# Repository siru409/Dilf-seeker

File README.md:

# Dilf-seeker
A near field multi beam ultra wideband fmcw radar detector using a novel near field focussed rotman lens

# to do maybe Hardware:
1. RX input limiter (strong RF sources close to dish)
2. FPGA compute port (if 4096 point FFT is not sufficient)

# to understand:
1: LOW if image rejection (ADL5380ACPZ-R7)

# to do Hardware:
1. RF traces ??
2. RX Chain finish
3. TX pll dimensions
4. MCU peripherals
5. Confirm charge pump circuit

# board tests:
0. does Balun Transformer output match IQ demod input impedance (yes)
1. Coupled TX IQ demod input <13dbm?
2. Test supplies first, only then add 0 ohm resistors to power sensitive components

# Design choices to make

1. Buttler matrix vs rotman lens -> rotman lense (potentially more array ports within reasonable space)
2. Vivaldi vs Horn Array-> Vivaldi array -> can be implemented in single PCB
3. 2 elliptical dishes vs combined rxtx vs TX dish + 8 fixed RX horns
4. Inductitity values for RX/TX inline buffers
5. 10uF caps 0805 -> price

# User manual

# simulation results

# Filtering

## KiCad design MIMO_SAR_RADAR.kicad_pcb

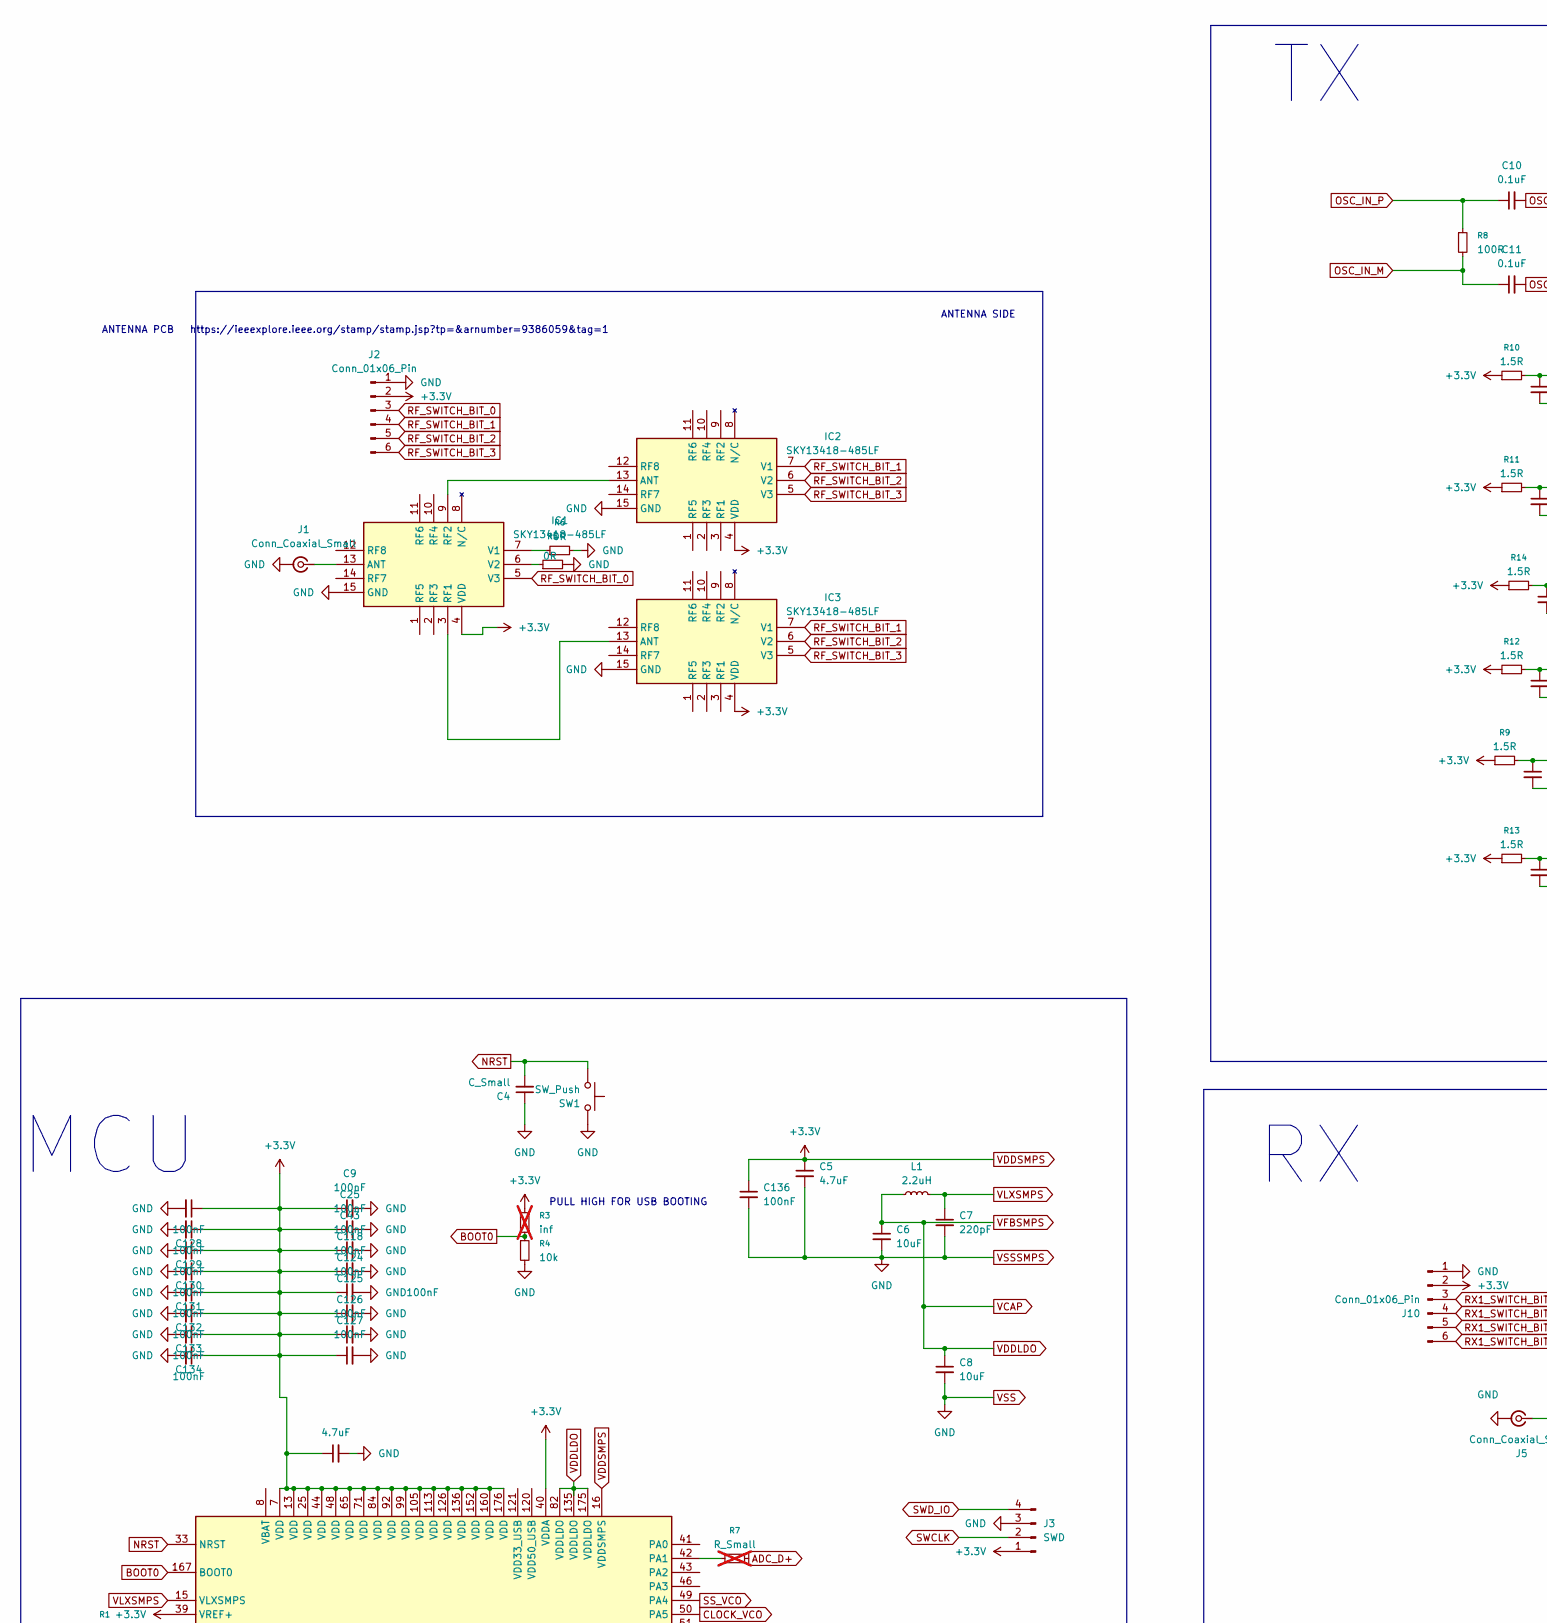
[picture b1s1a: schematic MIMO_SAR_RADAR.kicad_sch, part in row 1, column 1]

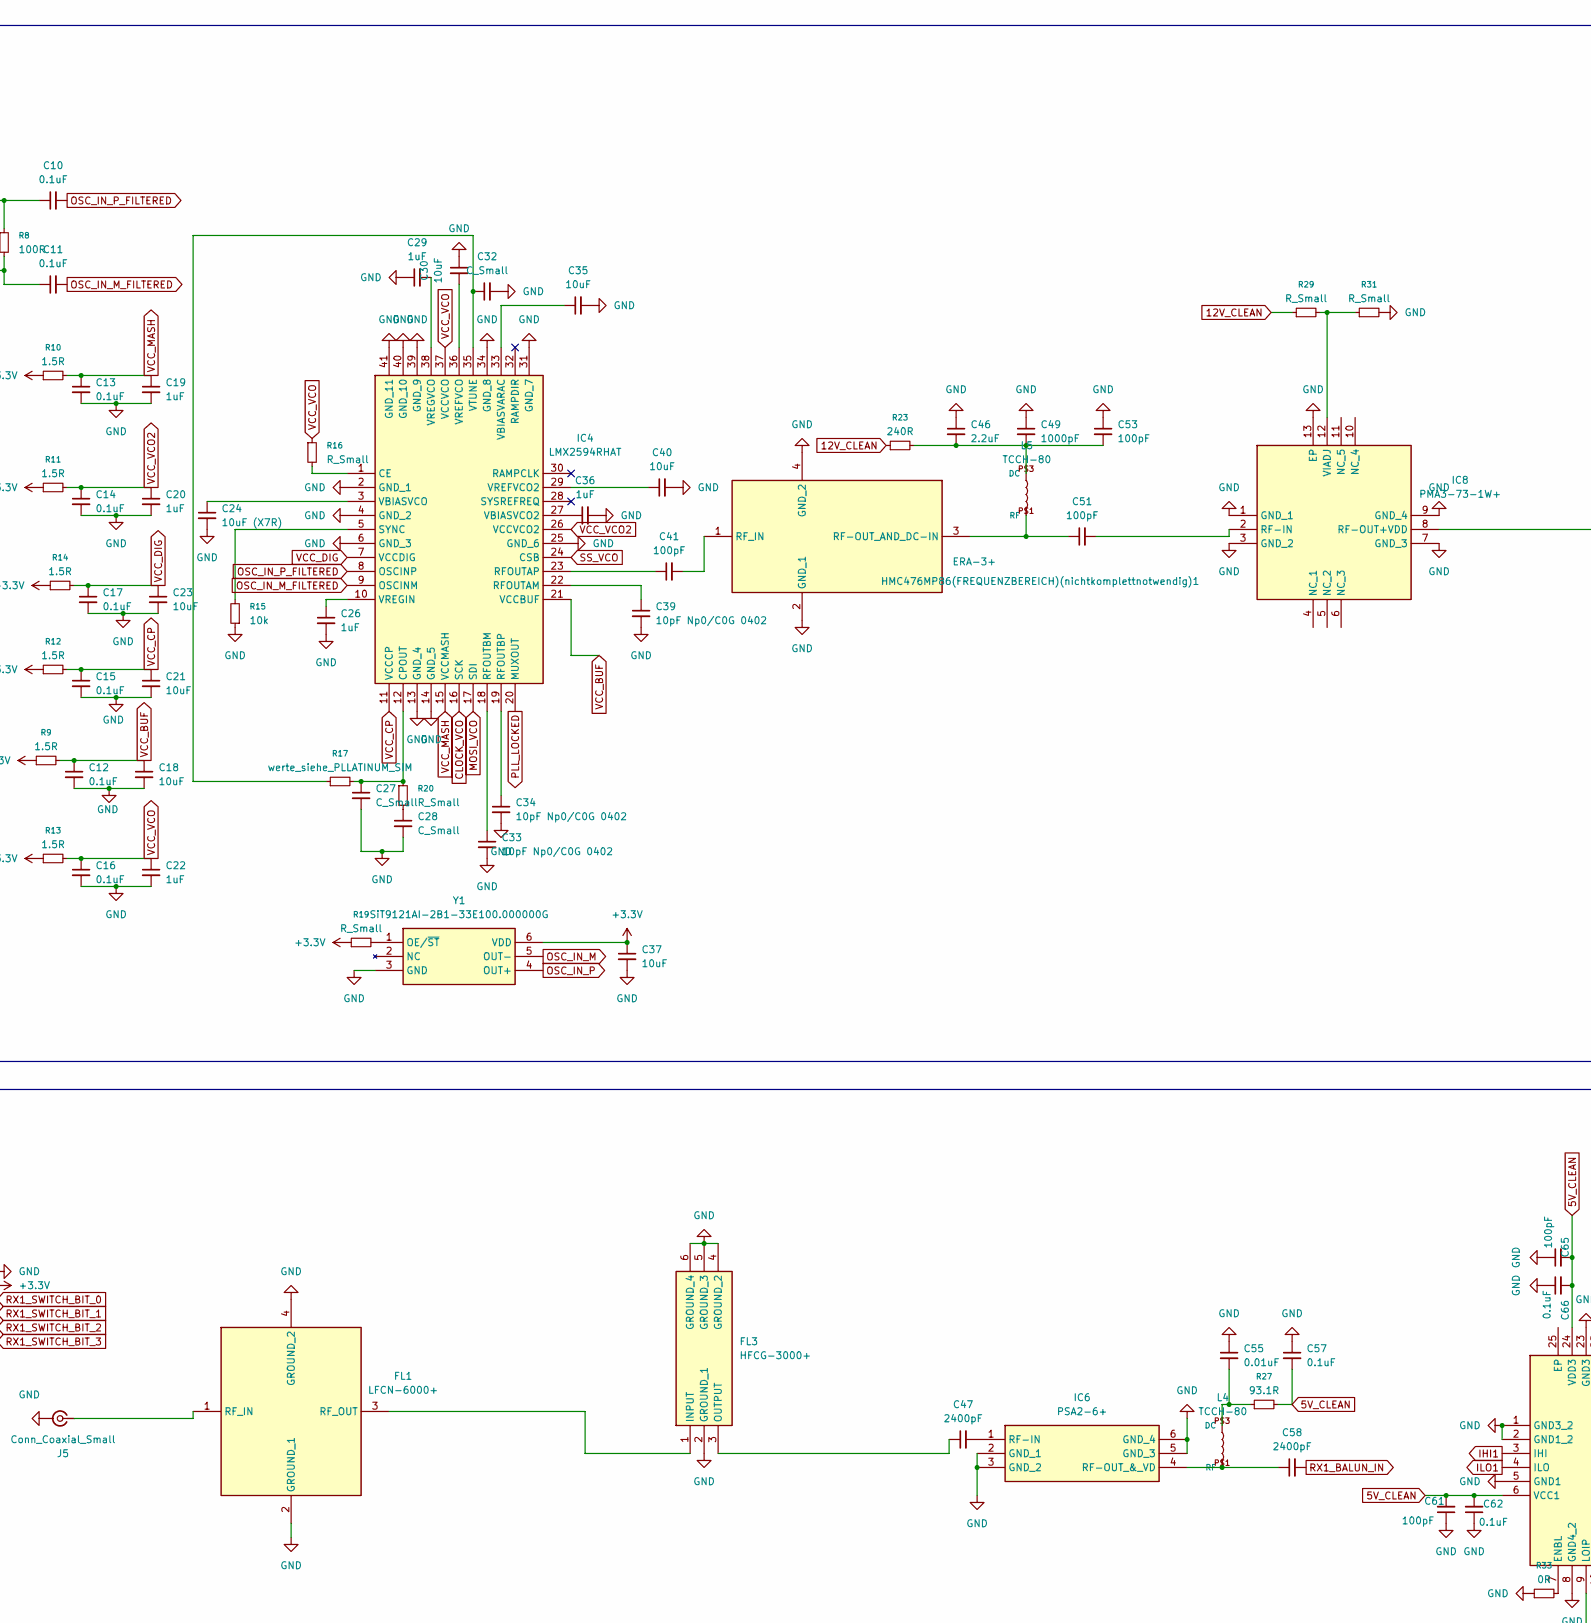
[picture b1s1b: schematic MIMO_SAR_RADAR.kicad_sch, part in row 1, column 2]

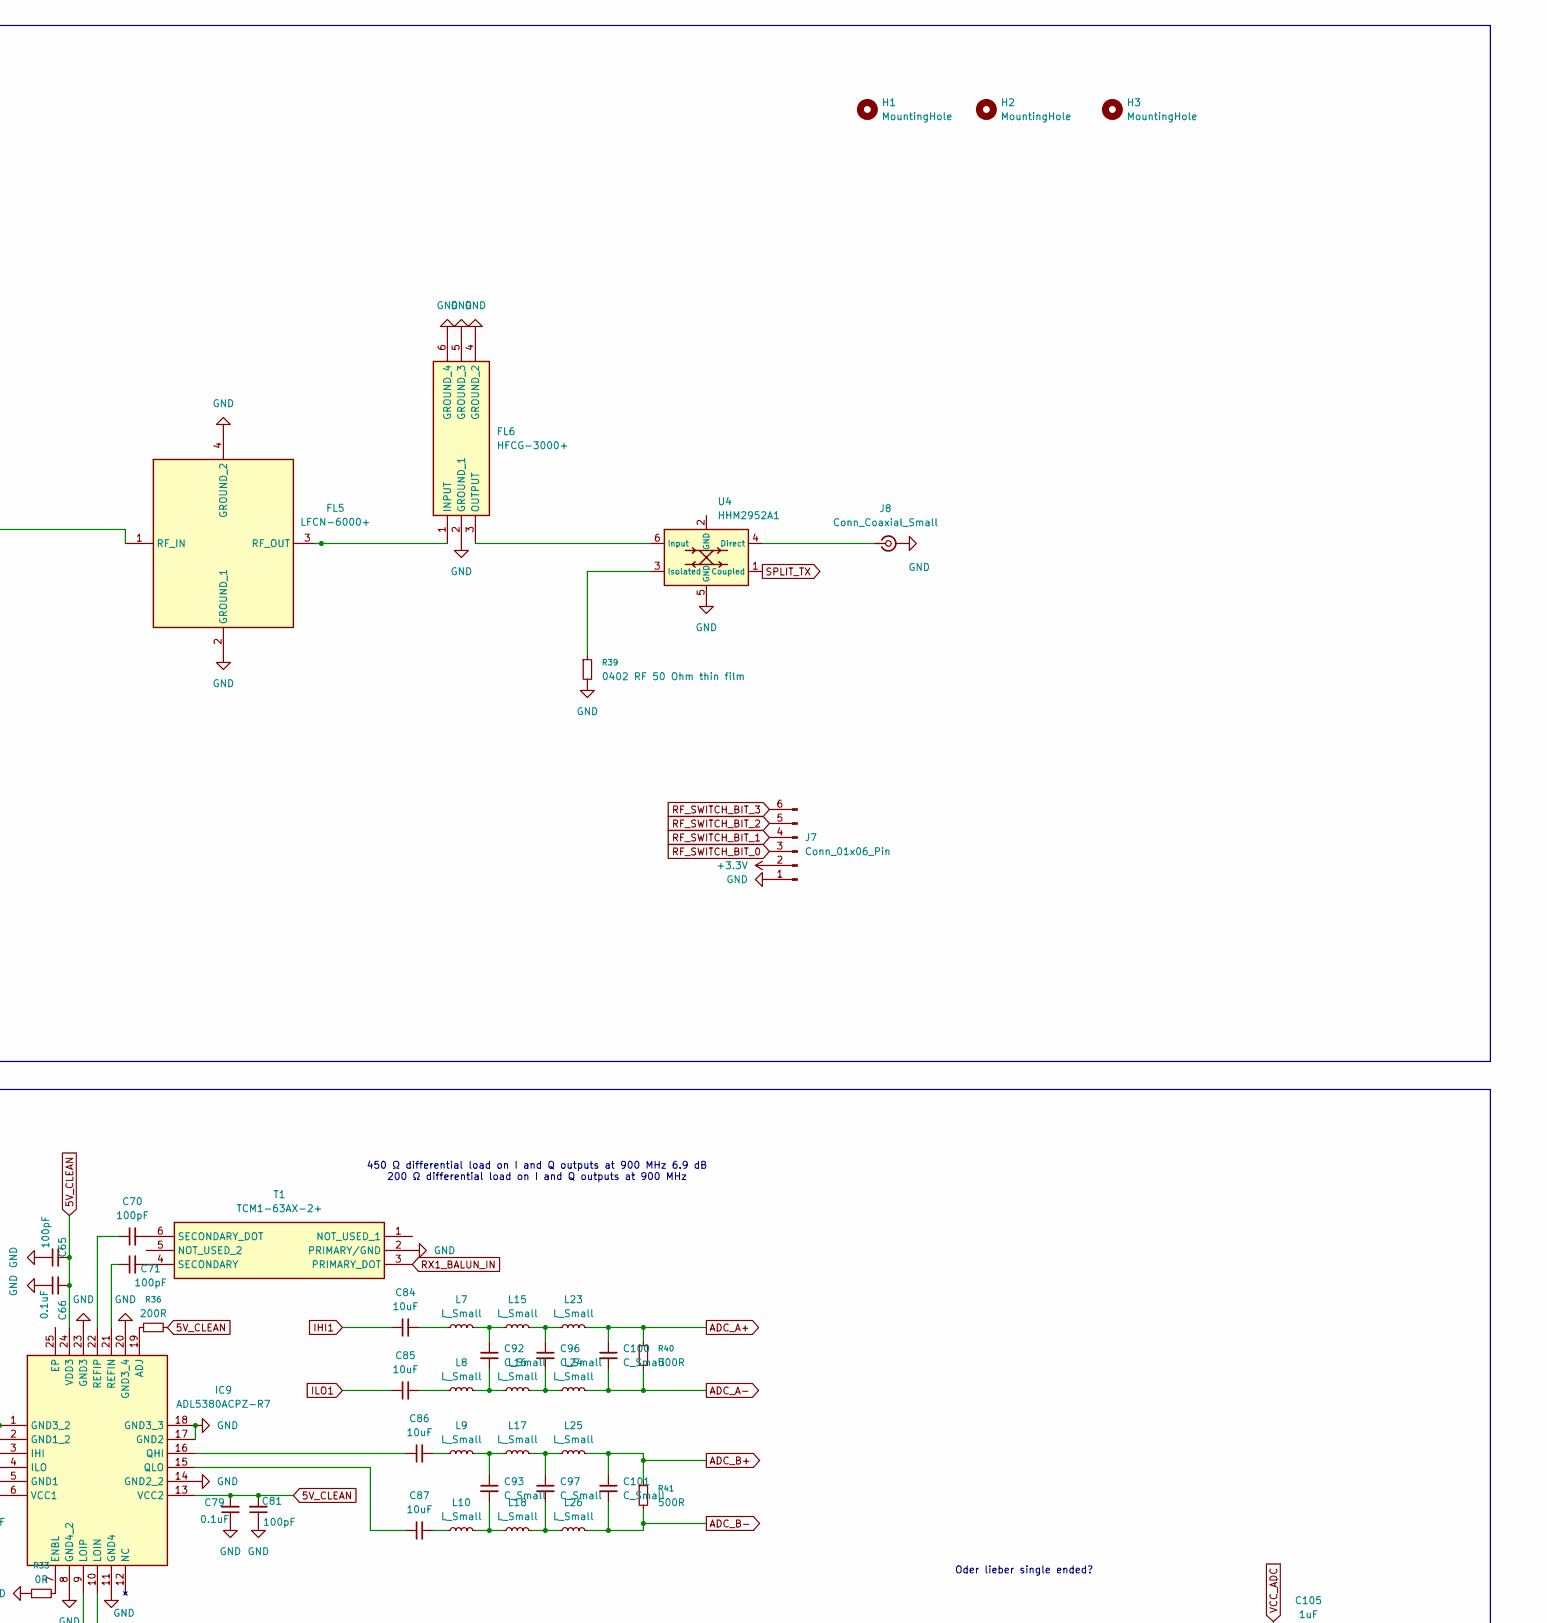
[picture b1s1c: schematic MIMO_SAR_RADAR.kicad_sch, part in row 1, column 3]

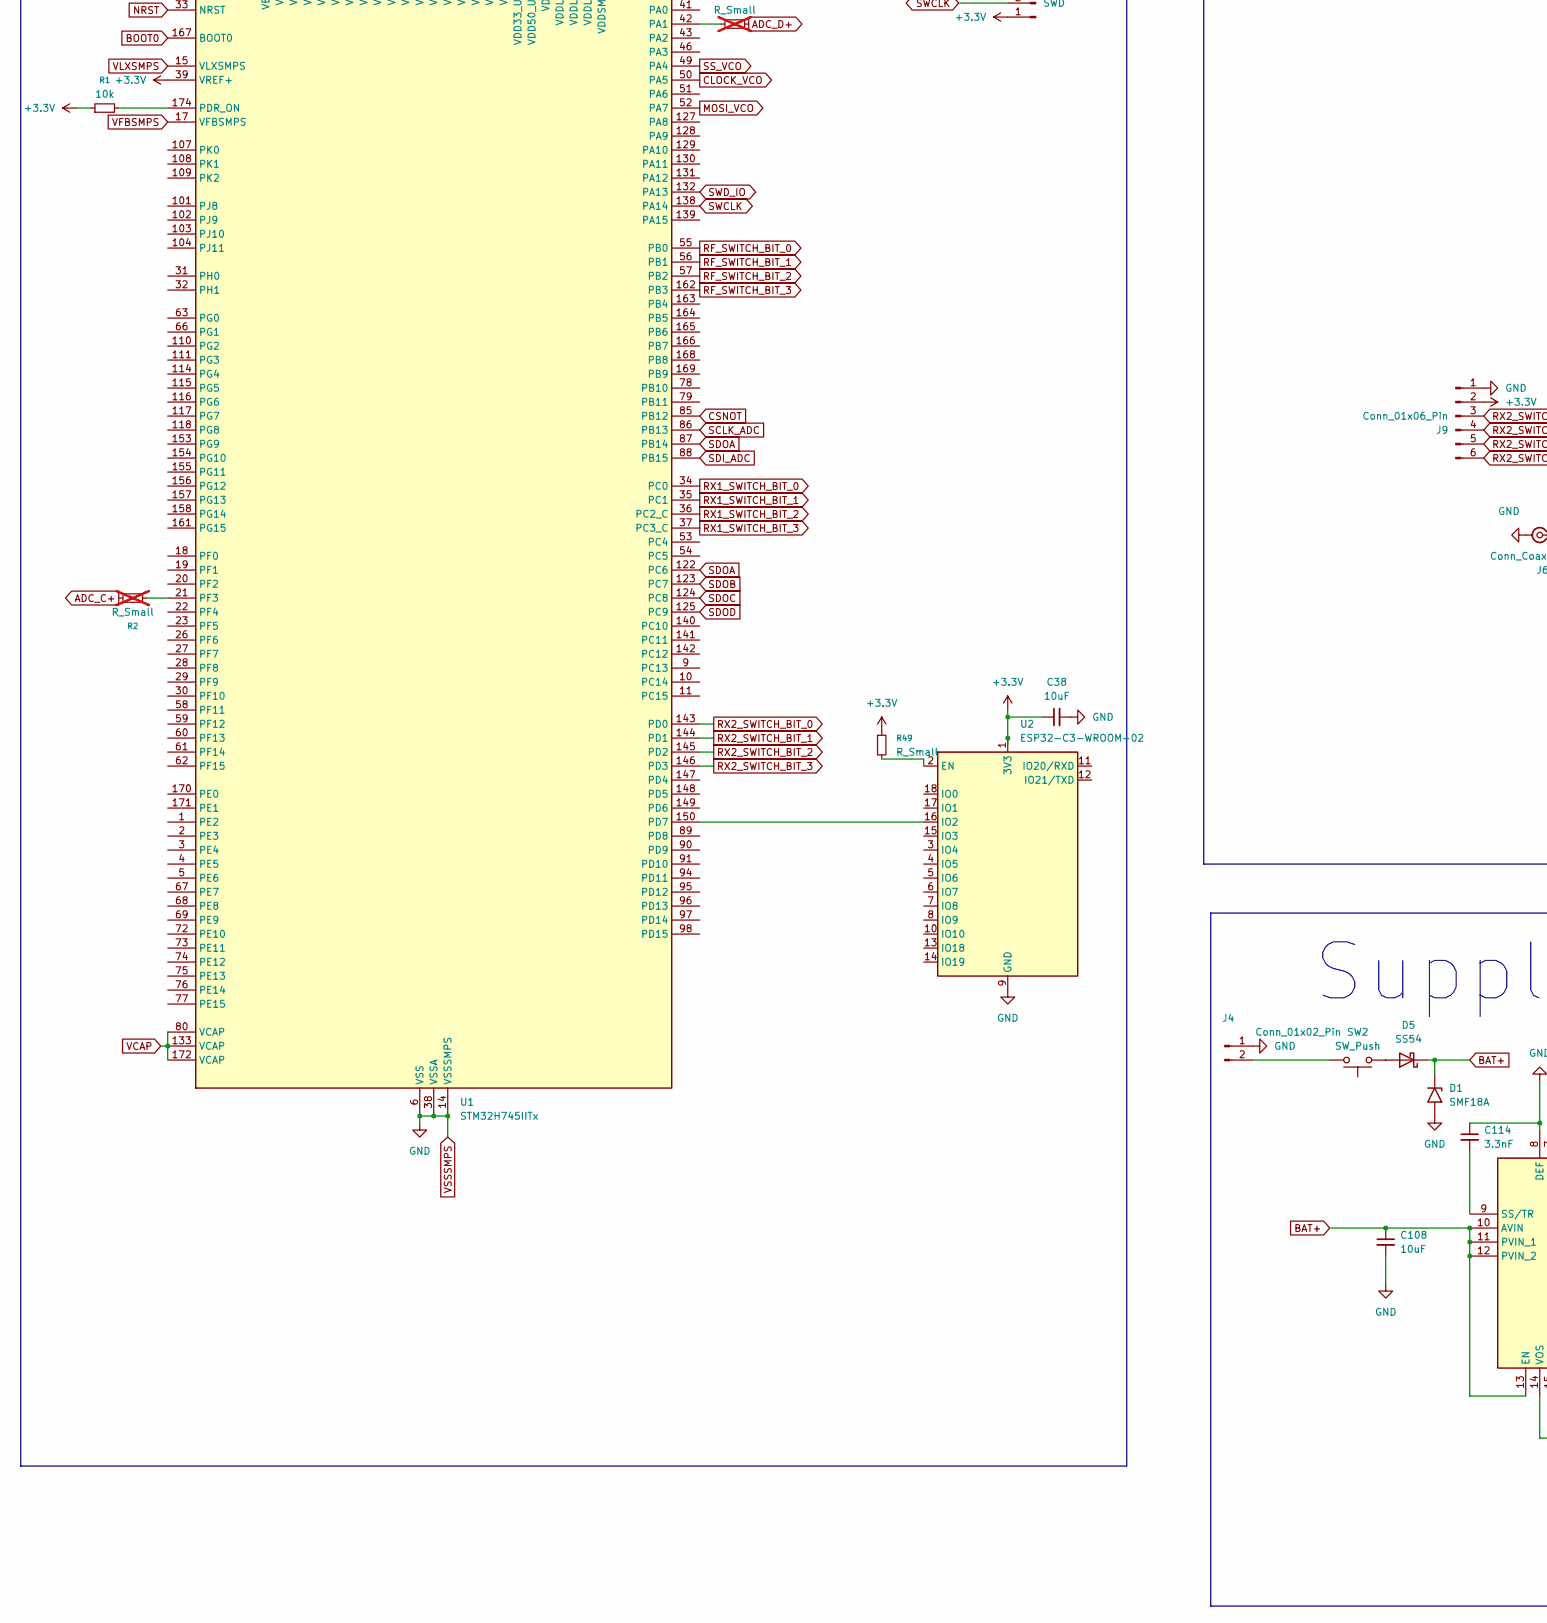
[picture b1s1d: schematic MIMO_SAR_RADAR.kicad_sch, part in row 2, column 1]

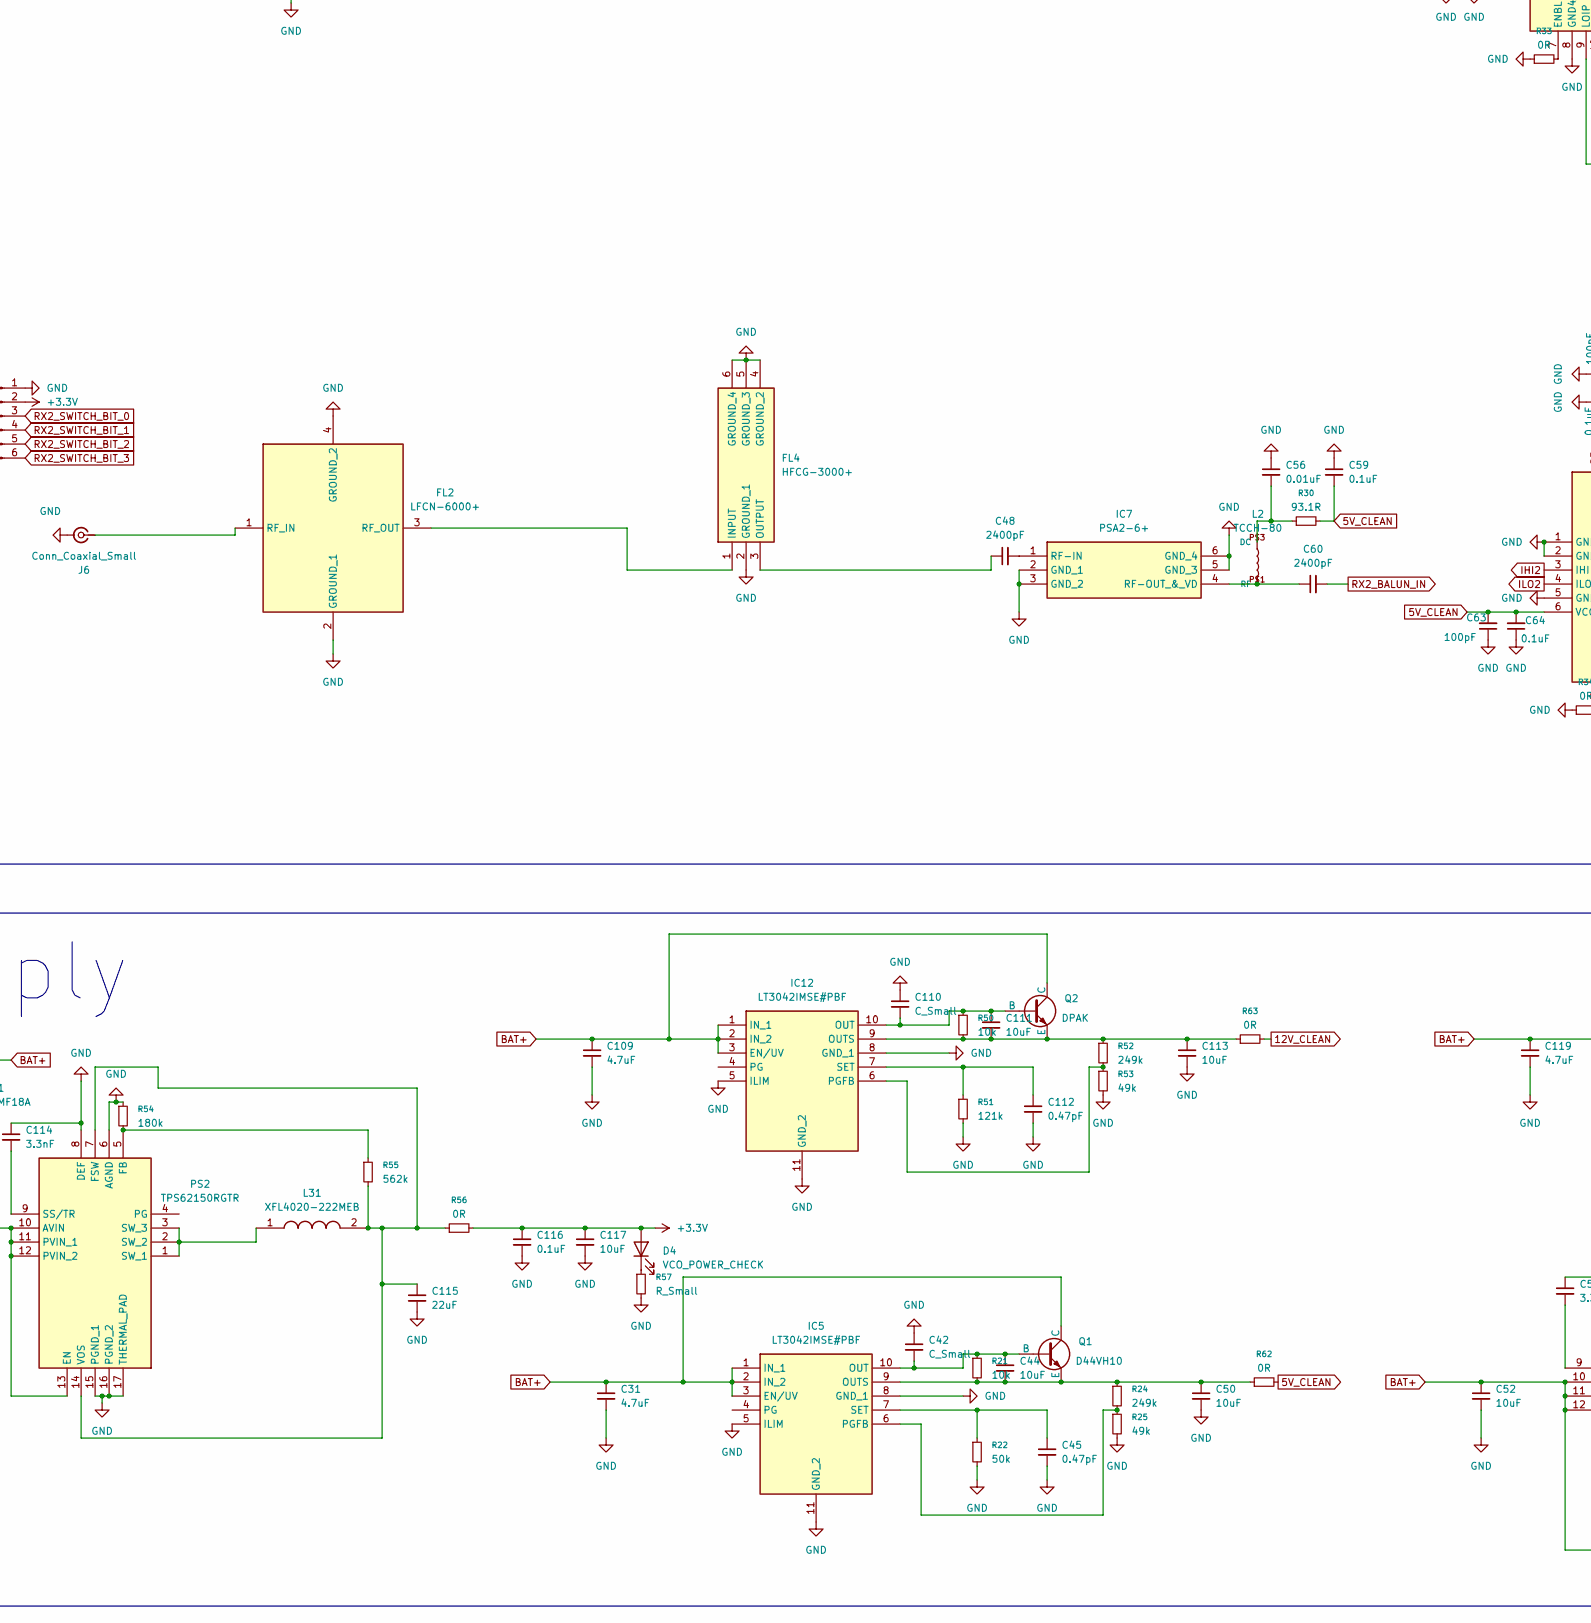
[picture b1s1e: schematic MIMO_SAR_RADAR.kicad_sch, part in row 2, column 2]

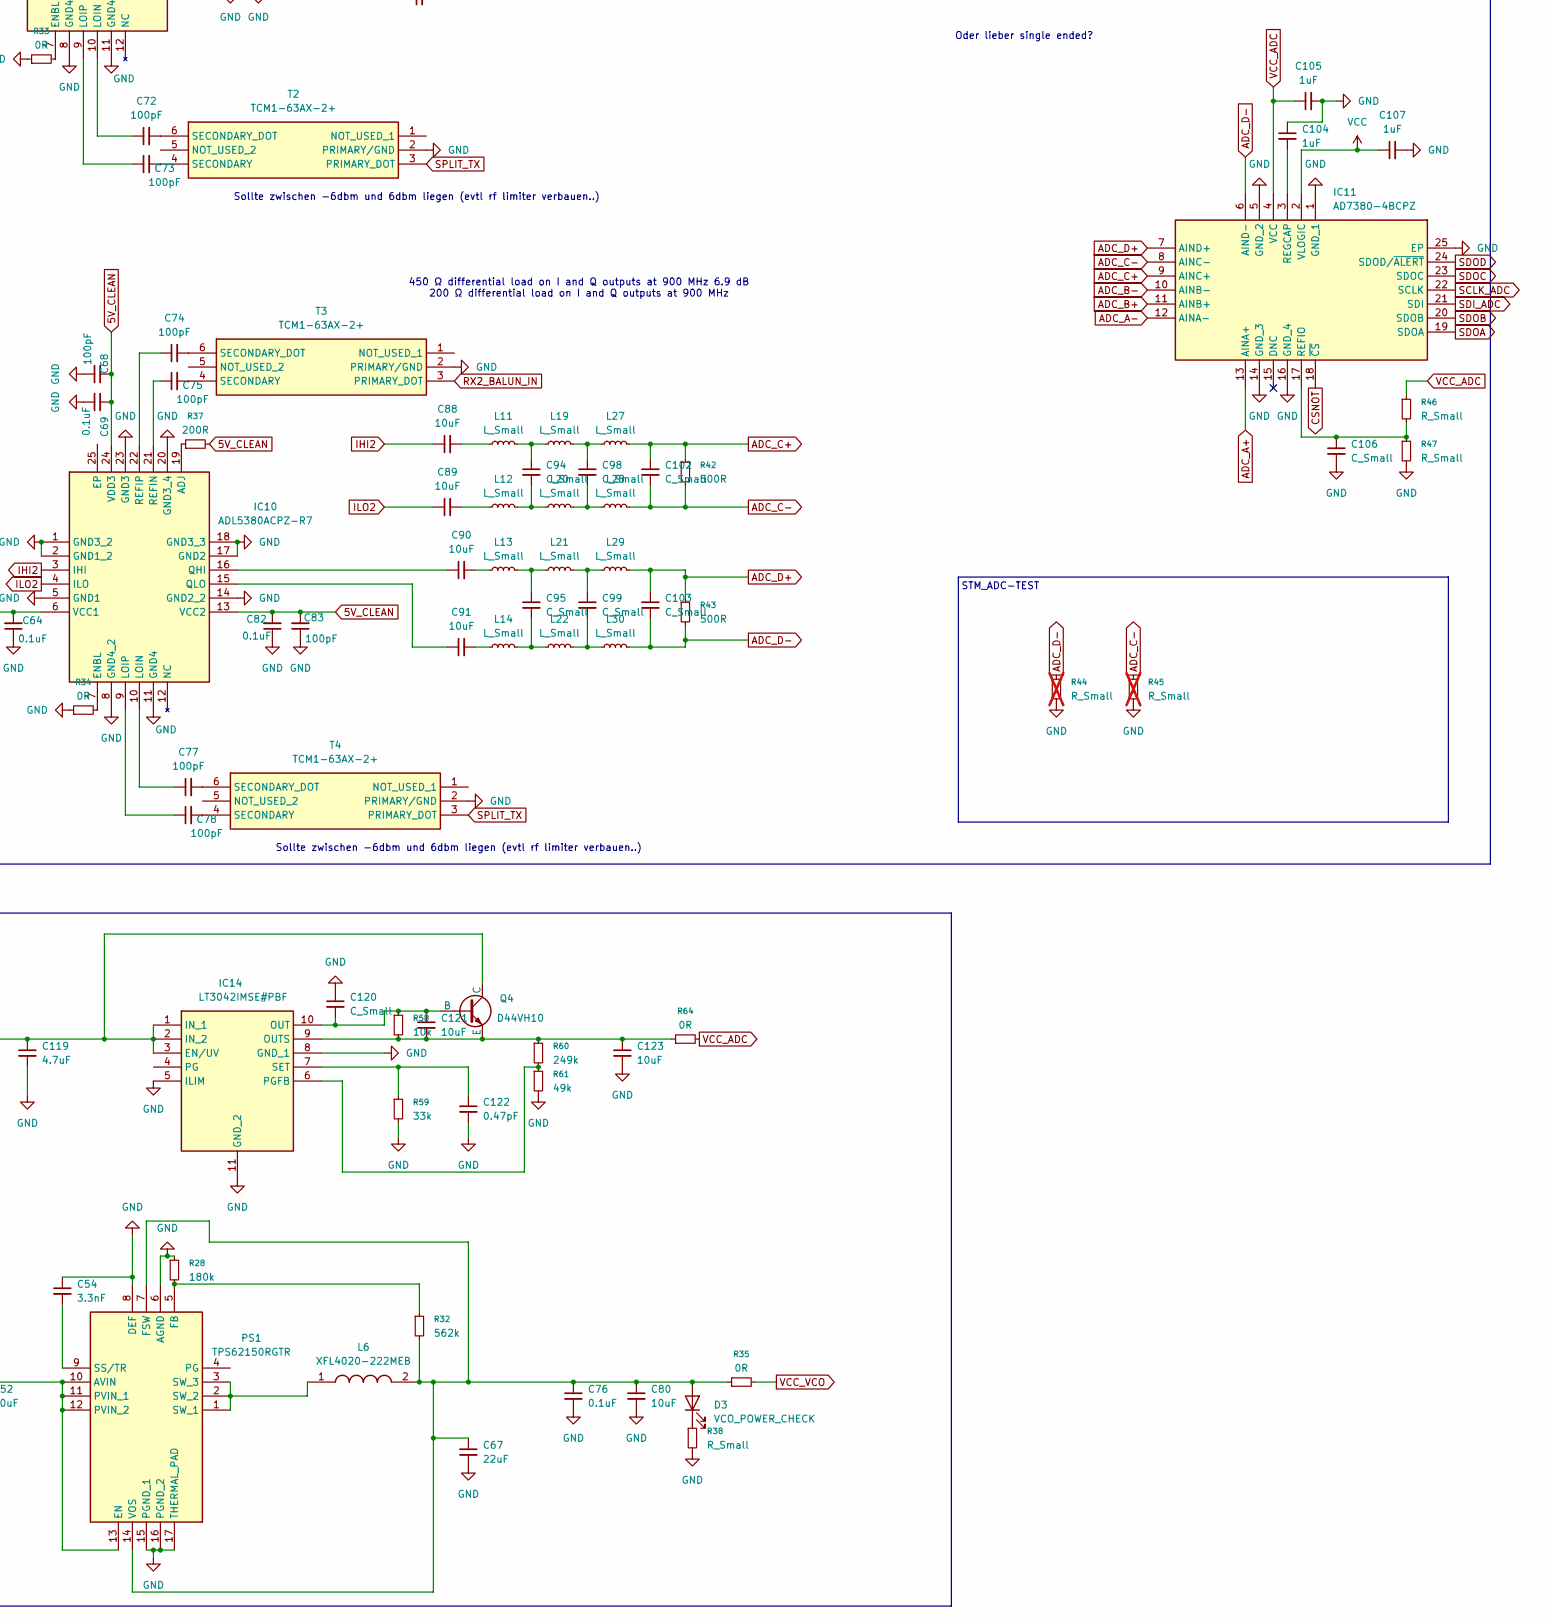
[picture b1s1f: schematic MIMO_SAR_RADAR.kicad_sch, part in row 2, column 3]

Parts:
C3, C5, C31, C109, C119: 4.7uF; C_0603_1608Metric
C4, C32, C42, C106, C110, C120: C_Small; C_0603_1608Metric
C6, C8, C18, C21, C23, C30, C35, C37, C38, C40, C44, C50, C52, C80, C108, C111, C113, C117, C121, C123: 10uF; C_0603_1608Metric
C7: 220pF; C_0603_1608Metric
C9, C25, C43, C118, C124, C125, C126, C127, C128, C129, C130, C131, C132, C133, C134, C135, C136: 100nF; C_0603_1608Metric
C10, C11: 0.1uF; C_0402_1005Metric
C12, C13, C14, C15, C16, C17, C57, C59, C62, C64, C66, C69, C76, C79, C82, C116: 0.1uF; C_0603_1608Metric
C19, C20, C22, C26, C29, C36, C104, C105, C107: 1uF; C_0603_1608Metric
C24: 10uF (X7R); C_0402_1005Metric
C27, C28, C92, C93, C94, C95, C96, C97, C98, C99, C100, C101, C102, C103: C_Small; C_0402_1005Metric
C33, C34, C39: 10pF Np0/C0G 0402; C_0402_1005Metric
C41, C51, C70, C71, C72, C73, C74, C75, C77, C78: 100pF; C_0402_1005Metric
C45, C112, C122: 0.47pF; C_0603_1608Metric
C46: 2.2uF; C_0603_1608Metric
C47, C58, C60: 2400pF; C_0402_1005Metric
C48: 2400pF; C_0603_1608Metric
C49: 1000pF; C_0603_1608Metric
C53, C61, C63, C65, C68, C81, C83: 100pF; C_0603_1608Metric
C54, C114: 3.3nF; C_0603_1608Metric
C55, C56: 0.01uF; C_0603_1608Metric
C67, C115: 22uF; C_0805_2012Metric
C84, C85, C86, C87, C88, C89, C90, C91: 10uF; C_0402_1005Metric
D1: SMF18A; D_SMF
D3, D4: VCO_POWER_CHECK; LED_0603_1608Metric
D5: SS54; D_SMA
FL1, FL2, FL5: LFCN-6000+; LFCN6000; Mouser Part Number 139-LFCN-6000
FL3, FL4, FL6: HFCG-3000+; HFCG3000; Mouser Part Number 139-HFCG-3000+
H1, H2, H3: MountingHole; MountingHole_3.2mm_M3_DIN965_Pad
HMC476MP86(FREQUENZBEREICH)(nichtkomplettnotwendig)1: ERA-3+; ERA3; Mouser Part Number 139-ERA-3
IC1, IC2, IC3: SKY13418-485LF; SKY13418485LF; Mouser Part Number 873-SKY13418-485LF
IC4: LMX2594RHAT; QFN-40-1EP_6x6mm_P0.5mm_EP4.6x4.6mm; Mouser Part Number 595-LMX2594RHAT
IC5, IC12, IC14: LT3042IMSE#PBF; SOP50P490X110-11N; Mouser Part Number 584-LT3042IMSE#PBF
IC6, IC7: PSA2-6+; SOT65P215X100-6N; Mouser Part Number 139-PSA2-6+
IC8: PMA3-73-1W+; QFN51P300X300X89-13N; Manufacturer_Part_Number PMA3-73-1W+
IC9, IC10: ADL5380ACPZ-R7; QFN50P400X400X100-25N; Mouser Part Number 584-ADL5380ACPZ-R7
IC11: AD7380-4BCPZ; QFN50P400X400X60-25N-D; Mouser Part Number 584-AD7380-4BCPZ
J1, J5, J6, J8: Conn_Coaxial_Small; SMA_Amphenol_132289_EdgeMount
J2, J7, J9, J10: Conn_01x06_Pin; JST_PH_B6B-PH-K_1x06_P2.00mm_Vertical
J3: SWD; JST_XH_B4B-XH-A_1x04_P2.50mm_Vertical
J4: Conn_01x02_Pin; AMASS_XT60-M_1x02_P7.20mm_Vertical
L1: 2.2uH; L_0805_2012Metric_Pad1.15x1.40mm_HandSolder
L2, L4, L5: TCCH-80; GU1604
L6, L31: XFL4020-222MEB; XFL4020-222ME; Mouser Part Number 994-XFL4020-222MEB
L7, L8, L9, L10, L11, L12, L13, L14, L15, L16, L17, L18, L19, L20, L21, L22, L23, L24, L25, L26, L27, L28, L29, L30: L_Small; L_0402_1005Metric
PS1, PS2: TPS62150RGTR; QFN50P300X300X100-17N-D; Mouser Part Number 595-TPS62150RGTR
Q1, Q4: D44VH10; TO-252-2
Q2: DPAK; TO-252-2
R1, R4, R15, R21, R50, R58: 10k; R_0603_1608Metric
R2, R7, R44, R45: R_Small; R_0603_1608Metric; not fitted
R3: inf; R_0603_1608Metric; not fitted
R5, R6, R33, R34, R35, R56, R62, R63, R64: 0R; R_0603_1608Metric
R8: 100R; R_0603_1608Metric
R9, R10, R11, R12, R13, R14: 1.5R; R_0603_1608Metric
R16, R19, R20, R29, R31, R38, R46, R47, R49, R57: R_Small; R_0603_1608Metric
R17: werte_siehe_PLLATINUM_SIM; R_0603_1608Metric
R22: 50k; R_0603_1608Metric
R23: 240R; R_0603_1608Metric
R24, R52, R60: 249k; R_0603_1608Metric
R25, R53, R61: 49k; R_0603_1608Metric
R27, R30: 93.1R; R_0805_2012Metric
R28, R54: 180k; R_0603_1608Metric
R32, R55: 562k; R_0603_1608Metric
R36, R37: 200R; R_0603_1608Metric
R39: 0402 RF 50 Ohm thin film; R_0402_1005Metric
R40, R41, R42, R43: 500R; R_0402_1005Metric
R51: 121k; R_0603_1608Metric
R59: 33k; R_0603_1608Metric
SW1: SW_Push; SW_SPST_CK_KXT3
SW2: SW_Push
T1, T2, T3, T4: TCM1-63AX-2+; TCM163AX2; Mouser Part Number 139-TCM1-63AX-2
U1: STM32H745IITx; LQFP-176_24x24mm_P0.5mm
U2: ESP32-C3-WROOM-02
U4: HHM2952A1
Y1: SiT9121AI-2B1-33E100.000000G; SiT9121AI2B133E100000000G; Mouser Part Number 788-9121AI-2B13E100G

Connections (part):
5V_CLEAN: C57.2, C59.2, C61.2, C62.2, C63.2, C64.2, C65.2, C66.2, C68.2, C69.2, C79.2, C81.2, C82.2, C83.2, IC9.6 (VCC1), IC9.13 (VCC2), IC9.24 (VDD3), IC10.6 (VCC1), IC10.13 (VCC2), IC10.24 (VDD3), R27.2, R30.2, R36.2, R37.2, R62.2
12V_CLEAN: R23.1, R29.1, R63.2
ADC_A+: C100.1, IC11.13 (AINA+), L23.2, R40.1
ADC_A-: C100.2, IC11.12 (AINA-), L24.2, R40.2
ADC_B+: C101.1, IC11.11 (AINB+), L25.2, R41.1
ADC_B-: C101.2, IC11.10 (AINB-), L26.2, R41.2
ADC_C+: C102.1, IC11.9 (AINC+), L27.2, R2.1, R42.1
ADC_C-: C102.2, IC11.8 (AINC-), L28.2, R42.2, R45.1
ADC_D+: C103.1, IC11.7 (AIND+), L29.2, R7.1, R43.1
ADC_D-: C103.2, IC11.6 (AIND-), L30.2, R43.2, R44.1
BAT+: C31.1, C52.1, C108.1, C109.1, C119.1, D1.1 (A1), D5.1 (K), IC5.1 (IN_1), IC5.2 (IN_2), IC5.3 (EN/UV), IC12.1 (IN_1), IC12.2 (IN_2), IC12.3 (EN/UV), IC14.1 (IN_1), IC14.2 (IN_2), IC14.3 (EN/UV), PS1.10 (AVIN), PS1.11 (PVIN_1), PS1.12 (PVIN_2), PS1.13 (EN), PS2.10 (AVIN), PS2.11 (PVIN_1), PS2.12 (PVIN_2), PS2.13 (EN), Q1.1 (C), Q2.1 (C), Q4.1 (C)
BOOT0: R3.2, R4.1, U1.167 (BOOT0)
CLOCK_VCO: IC4.16 (SCK), U1.50 (PA5)
CSNOT: IC11.18 (~CS), U1.85 (PB12)
IHI1: C84.1, IC9.3 (IHI)
IHI2: C88.1, IC10.3 (IHI)
ILO1: C85.1, IC9.4 (ILO)
ILO2: C89.1, IC10.4 (ILO)
MOSI_VCO: IC4.17 (SDI), U1.52 (PA7)
NRST: C4.2, SW1.1, U1.33 (NRST)
unnamed: C28.1, R20.2
unnamed: C84.2, L7.1
unnamed: C85.2, L8.1
unnamed: C86.2, L9.1
unnamed: C87.2, L10.1
unnamed: C88.2, L11.1
unnamed: C89.2, L12.1
unnamed: C90.2, L13.1
unnamed: C91.2, L14.1
unnamed: C92.1, L7.2, L15.1
unnamed: C92.2, L8.2, L16.1
unnamed: C93.1, L9.2, L17.1
unnamed: C93.2, L10.2, L18.1
unnamed: C94.1, L11.2, L19.1
unnamed: C94.2, L12.2, L20.1
unnamed: C95.1, L13.2, L21.1
unnamed: C95.2, L14.2, L22.1
unnamed: C96.1, L15.2, L23.1
unnamed: C96.2, L16.2, L24.1
unnamed: C97.1, L17.2, L25.1
unnamed: C97.2, L18.2, L26.1
unnamed: C98.1, L19.2, L27.1
unnamed: C98.2, L20.2, L28.1
unnamed: C99.1, L21.2, L29.1
unnamed: C99.2, L22.2, L30.1
unnamed: C67.1, C76.1, C80.1, D3.2 (A), L6.2, PS1.7 (FSW), PS1.14 (VOS), R32.2, R35.1
unnamed: D3.1 (K), R38.1
unnamed: D4.1 (K), R57.1
unnamed: D5.2 (A), SW2.1
unnamed: FL1.1 (RF_IN), J5.1 (In)
unnamed: FL1.3 (RF_OUT), FL3.1 (INPUT)
unnamed: FL2.1 (RF_IN), J6.1 (In)
unnamed: FL2.3 (RF_OUT), FL4.1 (INPUT)
unnamed: C47.1, FL3.3 (OUTPUT)
unnamed: C48.1, FL4.3 (OUTPUT)
unnamed: FL5.1 (RF_IN), IC8.8 (RF-OUT+VDD)
unnamed: FL5.3 (RF_OUT), FL6.1 (INPUT)
unnamed: FL6.3 (OUTPUT), U4.6 (Input)
unnamed: C51.1, HMC476MP86(FREQUENZBEREICH)(nichtkomple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.3 (RF-OUT_AND_DC-IN), L5.P$1 (RF)
unnamed: C41.2, HMC476MP86(FREQUENZBEREICH)(nichtkomple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.1 (RF_IN)
unnamed: IC1.13 (ANT), J1.1 (In)
unnamed: IC1.3 (RF1), IC3.13 (ANT)
unnamed: IC1.9 (RF2), IC2.13 (ANT)
unnamed: IC1.7 (V1), R6.1
unnamed: IC1.6 (V2), R5.1
unnamed: IC4.1 (CE), R16.2
unnamed: C27.1, IC4.12 (CPOUT), R17.2, R20.1
unnamed: C39.1, IC4.22 (RFOUTAM)
unnamed: C41.1, IC4.23 (RFOUTAP)
unnamed: C33.1, IC4.18 (RFOUTBM)
unnamed: C34.1, IC4.19 (RFOUTBP)
unnamed: IC4.5 (SYNC), R15.2
unnamed: C35.1, IC4.33 (VBIASVARAC)
unnamed: C36.1, IC4.27 (VBIASVCO2)
unnamed: C24.1, IC4.3 (VBIASVCO)
unnamed: C40.1, IC4.29 (VREFVCO2)
unnamed: C30.2, IC4.36 (VREFVCO)
unnamed: C26.1, IC4.10 (VREGIN)
unnamed: C29.2, IC4.38 (VREGVCO)
unnamed: C32.1, IC4.35 (VTUNE), R17.1
unnamed: C42.2, C44.1, IC5.10 (OUT), Q1.2 (B), R21.1
unnamed: C44.2, C50.1, IC5.9 (OUTS), Q1.3 (E), R21.2, R24.1, R62.1
unnamed: IC5.6 (PGFB), R24.2, R25.1
unnamed: C45.1, IC5.7 (SET), R22.1
unnamed: C47.2, IC6.1 (RF-IN)
unnamed: C58.1, IC6.4 (RF-OUT_&_VD), L4.P$1 (RF)
unnamed: C48.2, IC7.1 (RF-IN)
unnamed: C60.1, IC7.4 (RF-OUT_&_VD), L2.P$1 (RF)
unnamed: C51.2, IC8.2 (RF-IN)
unnamed: IC8.12 (VIADJ), R29.2, R31.1
unnamed: IC9.19 (ADJ), R36.1
unnamed: IC9.7 (ENBL), R33.2
unnamed: C72.1, IC9.10 (LOIN)
unnamed: C73.1, IC9.9 (LOIP)
unnamed: C86.1, IC9.16 (QHI)
unnamed: C87.1, IC9.15 (QLO)
unnamed: C71.1, IC9.21 (REFIN)
unnamed: C70.1, IC9.22 (REFIP)
unnamed: IC10.19 (ADJ), R37.1
unnamed: IC10.7 (ENBL), R34.2
unnamed: C77.1, IC10.10 (LOIN)
unnamed: C78.1, IC10.9 (LOIP)
unnamed: C90.1, IC10.16 (QHI)
unnamed: C91.1, IC10.15 (QLO)
unnamed: C75.1, IC10.21 (REFIN)
unnamed: C74.1, IC10.22 (REFIP)
unnamed: C106.1, IC11.17 (REFIO), R46.2, R47.1
unnamed: C104.2, IC11.3 (REGCAP)
unnamed: C110.2, C111.1, IC12.10 (OUT), Q2.2 (B), R50.1
unnamed: C111.2, C113.1, IC12.9 (OUTS), Q2.3 (E), R50.2, R52.1, R63.1
unnamed: IC12.6 (PGFB), R52.2, R53.1
unnamed: C112.1, IC12.7 (SET), R51.1
unnamed: C120.2, C121.1, IC14.10 (OUT), Q4.2 (B), R58.1
unnamed: C121.2, C123.1, IC14.9 (OUTS), Q4.3 (E), R58.2, R60.1, R64.1
unnamed: IC14.6 (PGFB), R60.2, R61.1
unnamed: C122.1, IC14.7 (SET), R59.1
unnamed: J4.2, SW2.2
unnamed: C56.2, L2.P$3 (DC), R30.1
unnamed: C55.2, L4.P$3 (DC), R27.1
unnamed: C46.2, C49.2, C53.2, L5.P$3 (DC), R23.2
unnamed: PS1.5 (FB), R28.2, R32.1
unnamed: C54.2, PS1.9 (SS/TR)
unnamed: L6.1, PS1.1 (SW_1), PS1.2 (SW_2), PS1.3 (SW_3)
unnamed: PS2.5 (FB), R54.2, R55.1
unnamed: C115.1, L31.2, PS2.7 (FSW), PS2.14 (VOS), R55.2, R56.1
unnamed: C114.2, PS2.9 (SS/TR)
unnamed: L31.1, PS2.1 (SW_1), PS2.2 (SW_2), PS2.3 (SW_3)
unnamed: C71.2, T1.4 (SECONDARY)
unnamed: C70.2, T1.6 (SECONDARY_DOT)
unnamed: C73.2, T2.4 (SECONDARY)
unnamed: C72.2, T2.6 (SECONDARY_DOT)
unnamed: C75.2, T3.4 (SECONDARY)
unnamed: C74.2, T3.6 (SECONDARY_DOT)
unnamed: C78.2, T4.4 (SECONDARY)
unnamed: C77.2, T4.6 (SECONDARY_DOT)
unnamed: R7.2, U1.42 (PA1)
unnamed: U1.150 (PD7), U2.16 (IO2)
unnamed: R1.2, U1.174 (PDR_ON)
unnamed: R2.2, U1.21 (PF3)
unnamed: R49.2, U2.2 (EN)
unnamed: R39.1, U4.3 (Isolated)
unnamed: R19.2, Y1.1 (OE/~ST)
OSC_IN_M: C11.1, R8.2, Y1.5 (OUT-)
OSC_IN_M_FILTERED: C11.2, IC4.9 (OSCINM)
OSC_IN_P: C10.1, R8.1, Y1.4 (OUT+)
OSC_IN_P_FILTERED: C10.2, IC4.8 (OSCINP)
PLL_LOCKED: IC4.20 (MUXOUT)
RF_SWITCH_BIT_0: IC1.5 (V3), J2.3, J7.3, U1.55 (PB0)
RF_SWITCH_BIT_1: IC2.7 (V1), IC3.7 (V1), J2.4, J7.4, U1.56 (PB1)
RF_SWITCH_BIT_2: IC2.6 (V2), IC3.6 (V2), J2.5, J7.5, U1.57 (PB2)
RF_SWITCH_BIT_3: IC2.5 (V3), IC3.5 (V3), J2.6, J7.6, U1.162 (PB3)
RX1_BALUN_IN: C58.2, T1.3 (PRIMARY_DOT)
RX1_SWITCH_BIT_0: J10.3, U1.34 (PC0)
RX1_SWITCH_BIT_1: J10.4, U1.35 (PC1)
RX1_SWITCH_BIT_2: J10.5, U1.36 (PC2_C)
RX1_SWITCH_BIT_3: J10.6, U1.37 (PC3_C)
RX2_BALUN_IN: C60.2, T3.3 (PRIMARY_DOT)
RX2_SWITCH_BIT_0: J9.3, U1.143 (PD0)
RX2_SWITCH_BIT_1: J9.4, U1.144 (PD1)
RX2_SWITCH_BIT_2: J9.5, U1.145 (PD2)
RX2_SWITCH_BIT_3: J9.6, U1.146 (PD3)
SCLK_ADC: IC11.22 (SCLK), U1.86 (PB13)
SDI_ADC: IC11.21 (SDI), U1.88 (PB15)
SDOA: IC11.19 (SDOA), U1.87 (PB14), U1.122 (PC6)
SDOB: IC11.20 (SDOB), U1.123 (PC7)
SDOC: IC11.23 (SDOC), U1.124 (PC8)
SDOD: IC11.24 (SDOD/~ALERT), U1.125 (PC9)
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
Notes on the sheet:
Sollte zwischen -6dbm und 6dbm liegen (evtl rf limiter verbauen..)
450 Ω differential load on I and Q outputs at 900 MHz 6.9 dB 200 Ω differential load on I and Q outputs at 900 MHz
MCU
ANTENNA SIDE
ANTENNA PCB https://ieeexplore.ieee.org/stamp/stamp.jsp?tp=&arnumber=9386059&tag=1
PULL HIGH FOR USB BOOTING
Oder lieber single ended?
STM_ADC-TEST
Supply

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
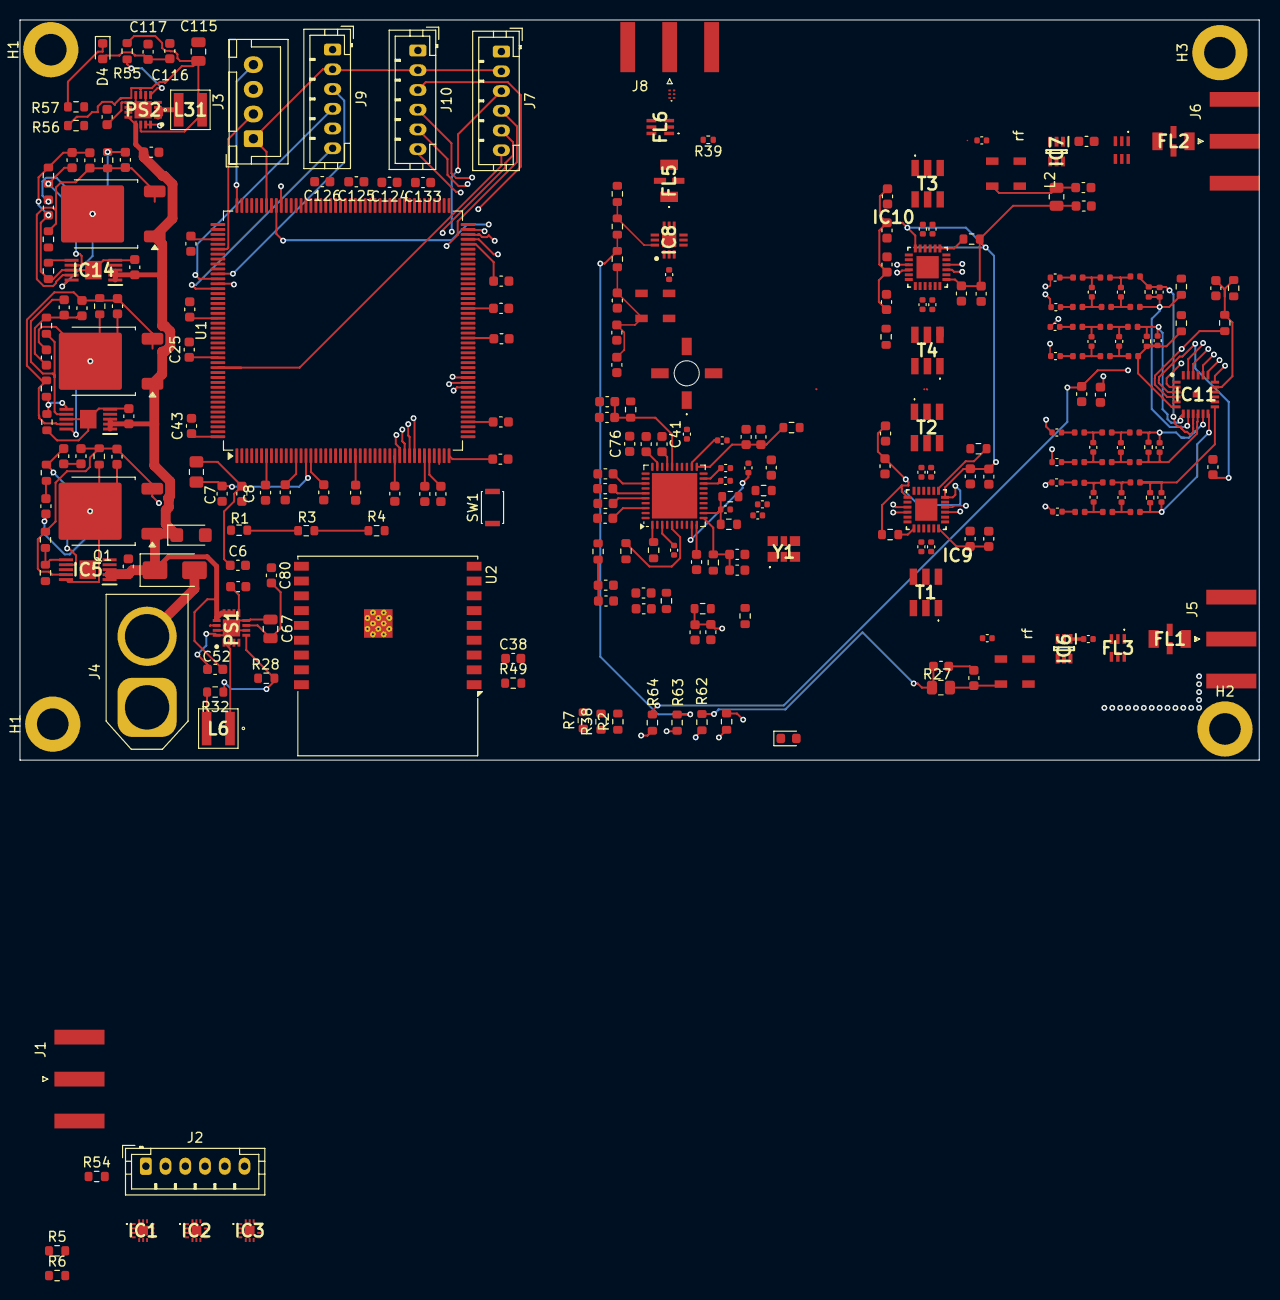
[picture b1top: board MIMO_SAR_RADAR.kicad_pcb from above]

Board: 4 copper layers, 125.6 x 75.0 mm, 277 parts (0 on the bottom side), 181 nets.

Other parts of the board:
H1#2: MountingHole; MountingHole_3.2mm_M3_DIN965_Pad
